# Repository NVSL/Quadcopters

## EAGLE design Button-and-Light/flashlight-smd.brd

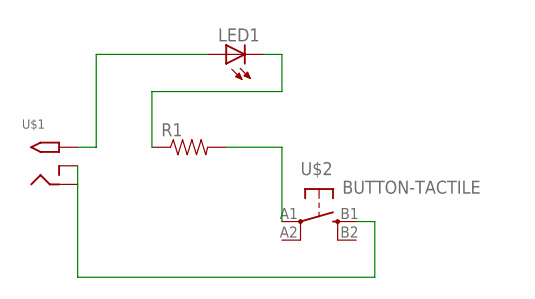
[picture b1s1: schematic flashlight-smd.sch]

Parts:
LED1: LED5MM
R1: RESISTORAXIAL-0.3; AXIAL-0.3
U$1: 2.1MMJACKTHM; PJ-102A
U$2: BUTTON-TACTILE; TACTILE_SWITCH_TALL

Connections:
unnamed: R1.P$2 (2), U$2.A1
unnamed: LED1.K (C), R1.P$1 (1)
unnamed: LED1.A, U$1.TIP
unnamed: U$1.RING, U$1.RING_SW, U$2.B1 (S)

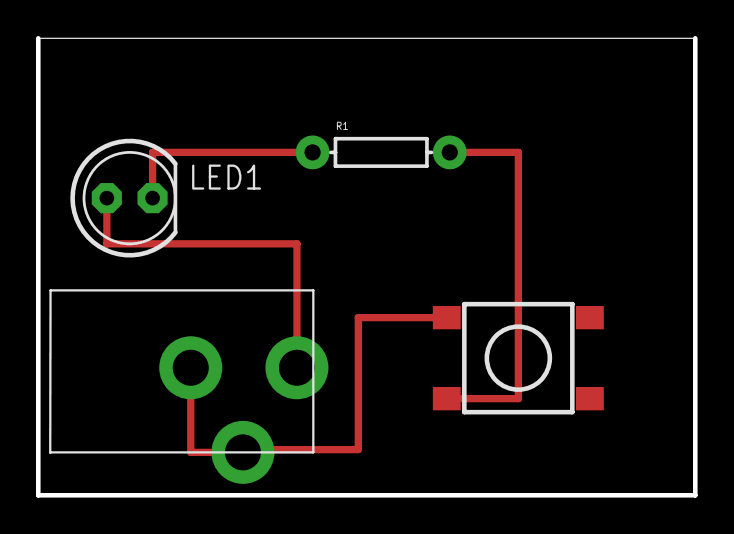
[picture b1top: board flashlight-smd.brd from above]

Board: 2 copper layers, 36.5 x 25.4 mm, 4 parts (0 on the bottom side), 4 nets.

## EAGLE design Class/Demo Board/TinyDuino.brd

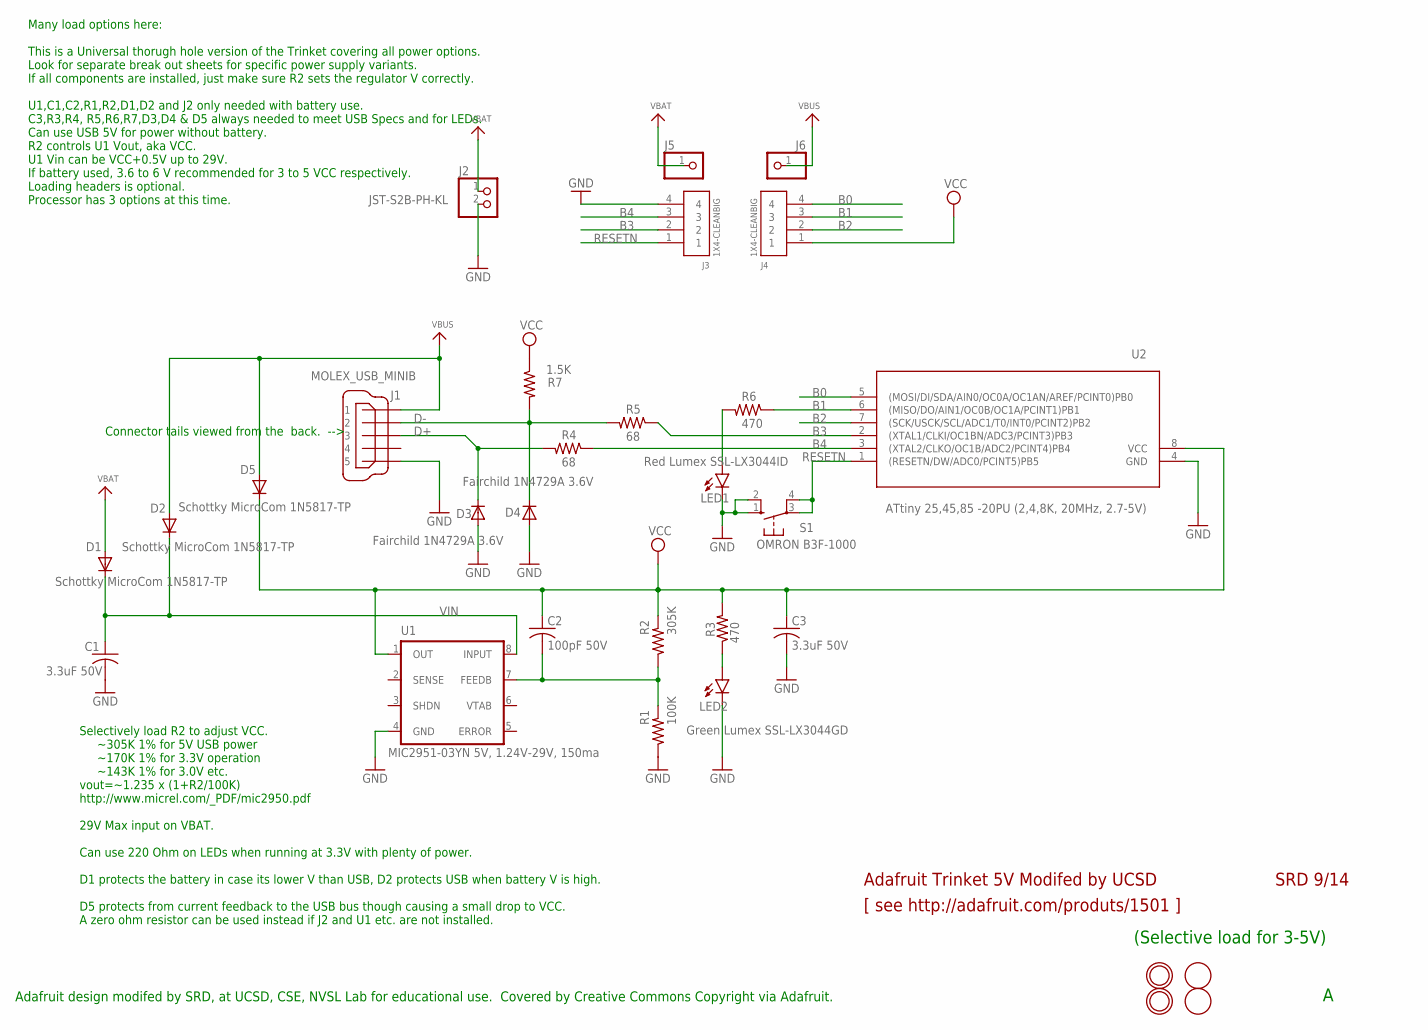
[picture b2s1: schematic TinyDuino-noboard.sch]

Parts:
C1, C3: 3.3uF 50V; C050-025X075; PARTNO FK20X7R1H335K
C2: 100pF 50V; C050-025X075; PARTNO FK28C0G1H101J
D1, D2, D5: Schottky MicroCom 1N5817-TP; DO41-7.6; PARTNO 1N5817-TP
D3, D4: Fairchild 1N4729A 3.6V; DO41-7.6; PARTNO 1N4729A
J1: MOLEX_USB_MINIB; 32005-601-ROUND; PARTNO 0548190519
J2: JST-S2B-PH-KL; JST_S2B_PH_KL; PARTNO JST_S2B_PH_KL
J3, J4: 1X4-CLEANBIG; 1X04-CLEANBIG
J5, J6: PINHD-1X1CB; 1X01-CLEANBIG
LED1: Red Lumex SSL-LX3044ID; LED3MM; PARTNO SSL-LX3044ID
LED2: Green Lumex SSL-LX3044GD; LED3MM; PARTNO SSL-LX3044GD
R1: 100K; 0204/7; PARTNO MFR-25FBF52-100K
R2: 305K; 0204/7; PARTNO MFR-25FBF52-301K
R3, R6: 470; 0204/7; PARTNO CFR-12JB-52-470R
R4, R5: 68; 0204/7; PARTNO CFR-12JB-52-68R
R7: 1.5K; 0204/7; PARTNO CFR-12JB-52-1K5
S1: OMRON B3F-1000; B3F-10XX; PARTNO B3F-1000
U1: MIC2951-03YN 5V, 1.24V-29V, 150ma; DIL08; PARTNO MIC2951-03YN
U2: ATtiny 25,45,85 -20PU (2,4,8K, 20MHz, 2.7-5V); DIL08; PARTNO ATTINY85-20PU-ND
Z1, Z2: MOUNTINGHOLE2.0; MOUNTINGHOLE_2.0_PLATED
Z3, Z4: FIDUCIAL; FIDUCIAL_1MM

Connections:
B0: J4.4, U2.5 ((MOSI/DI/SDA/AIN0/OC0A/OC1AN/AREF/PCINT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)
B1: J4.3, R6.1, U2.6 ((MISO/DO/AIN1/OC0B/OC1A/PCINT1)PB1)
B2: J4.2, U2.7 ((SCK/USCK/SCL/ADC1/T0/INT0/PCINT2)PB2)
B3: J3.2, R5.1, U2.2 ((XTAL1/CLKI/OC1BN/ADC3/PCINT3)PB3)
B4: J3.3, R4.1, U2.3 ((XTAL2/CLKO/OC1B/ADC2/PCINT4)PB4)
D+: D3.C, J1.3, R4.2
D-: D4.C, J1.2, R5.2, R7.2
GND: C1.2, C3.2, D3.A, D4.A, J1.5, J2.2, J3.4, LED1.K (C), LED2.K (C), R1.1, S1.1 (S), S1.2 (S1), U1.4 (GND), U2.4 (GND)
unnamed: LED1.A, R6.2
unnamed: LED2.A, R3.1
unnamed: C2.2, R1.2, R2.1, U1.7 (FEEDB)
RESETN: J3.1, S1.3, S1.4 (P1), U2.1 ((RESETN/DW/ADC0/PCINT5)PB5)
VBAT: D1.A, J2.1, J5.1
VBUS: D2.A, D5.A, J1.1, J6.1
VCC: C2.1, C3.1, D5.C, J4.1, R2.2, R3.2, R7.1, U1.1 (OUT), U2.8 (VCC)
VIN: C1.1, D1.C, D2.C, U1.8 (INPUT)

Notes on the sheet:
Adafruit Trinket 5V Modifed by UCSD
[ see http://adafruit.com/produts/1501 ]
SRD 9/14
Adafruit design modifed by SRD, at UCSD, CSE, NVSL Lab for educational use. Covered by Creative Commons Copyright via Adafruit.
(Selective load for 3-5V)
Selectively load R2 to adjust VCC. ~305K 1% for 5V USB power ~170K 1% for 3.3V operation ~143K 1% for 3.0V etc. vout=~1.235 x (1+R2/100K) http://www.micrel.com/_PDF/mic2950.pdf 29V Max input on VBAT. Can use 220 Ohm on LEDs when running at 3.3V with plenty of power. D1 protects the battery in case 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
Connector tails viewed from the back. -->
Many load options here: This is a Universal thorugh hole version of the Trinket covering all power options. Look for separate break out sheets for specific power supply variants. If all components are installed, just make sure R2 sets the regulator V correctly. U1,C1,C2,R1,R2,D1,D2 and J2 only need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

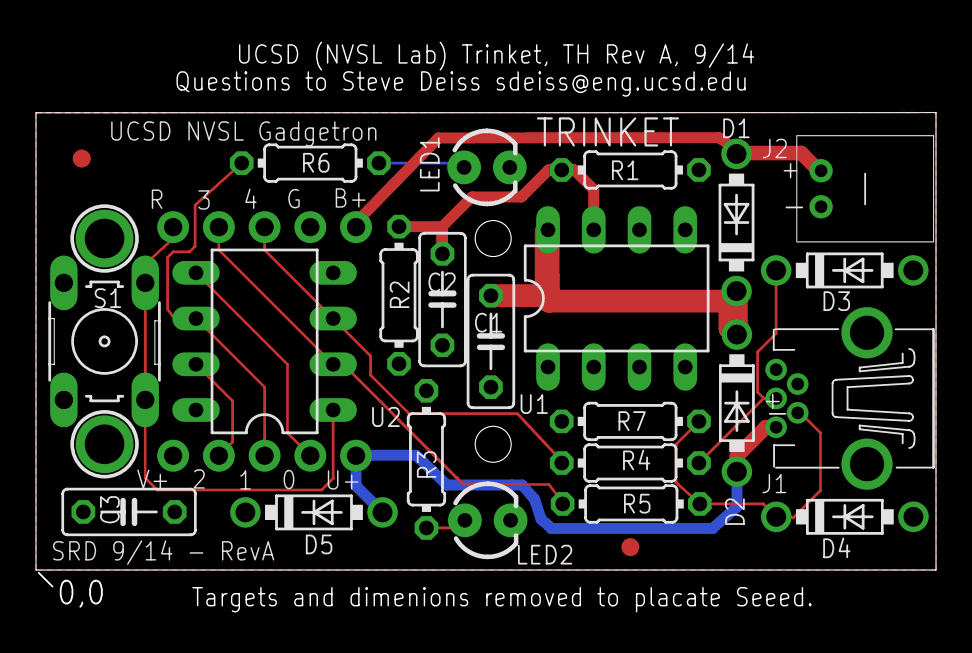
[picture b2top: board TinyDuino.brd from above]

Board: 2 copper layers, 50.0 x 26.3 mm, 30 parts (0 on the bottom side), 16 nets.

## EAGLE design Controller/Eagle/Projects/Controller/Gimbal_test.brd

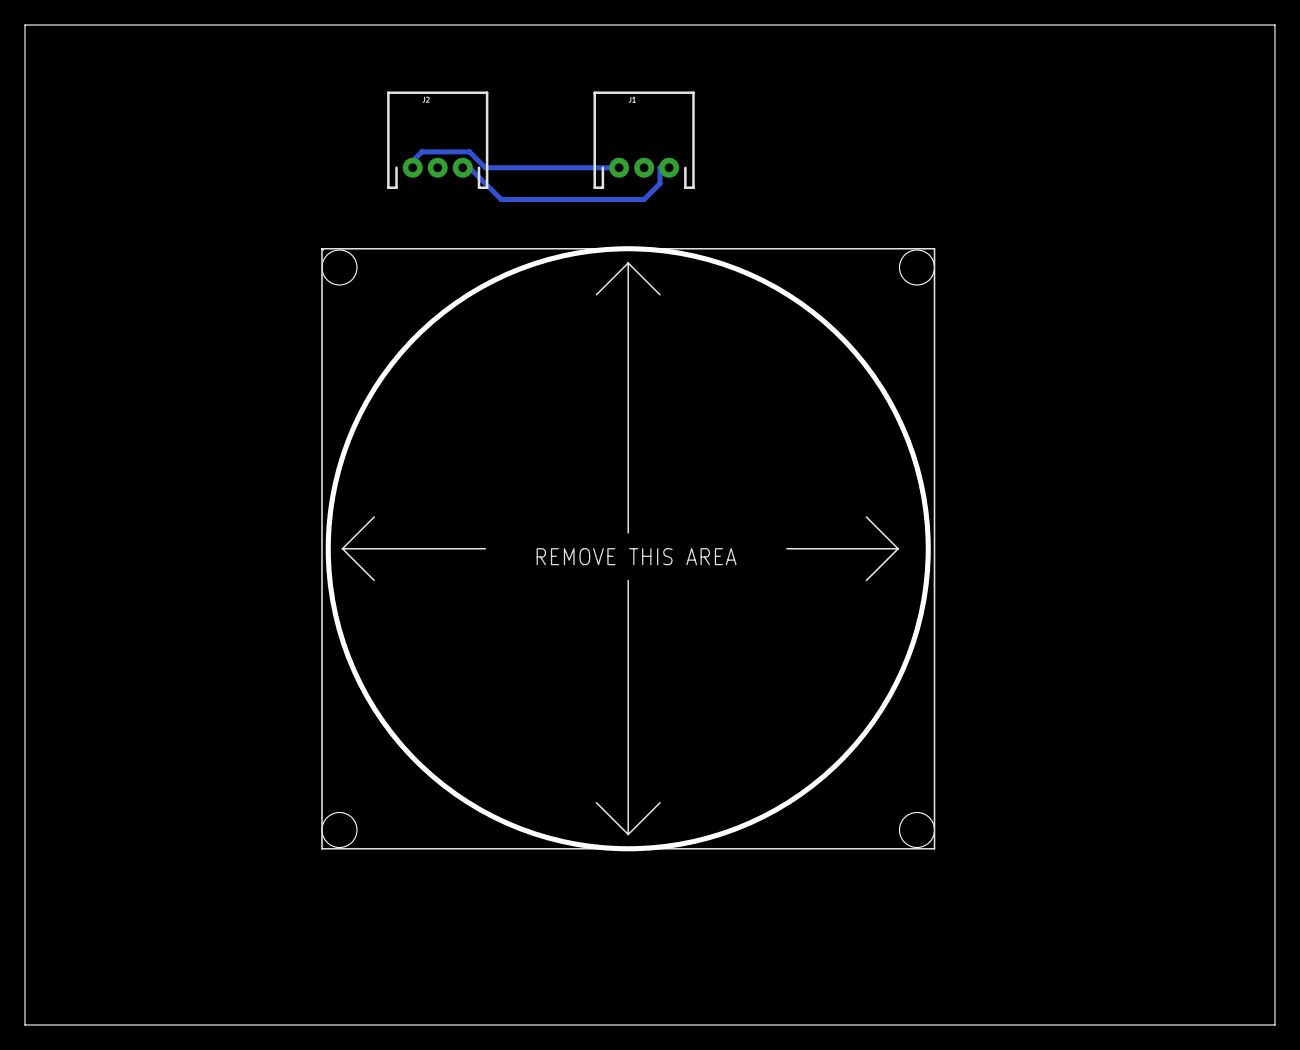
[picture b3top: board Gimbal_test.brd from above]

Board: 2 copper layers, 100.0 x 80.0 mm, 3 parts (0 on the bottom side), 2 nets.

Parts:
J1, J2: GIMBAL_3PIN; JST-3-PTH
U$1: GIMBAL_MOUNT; GIMBAL_FOOTPRINT

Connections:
GND: J1.3, J2.3
VDD: J1.1, J2.1

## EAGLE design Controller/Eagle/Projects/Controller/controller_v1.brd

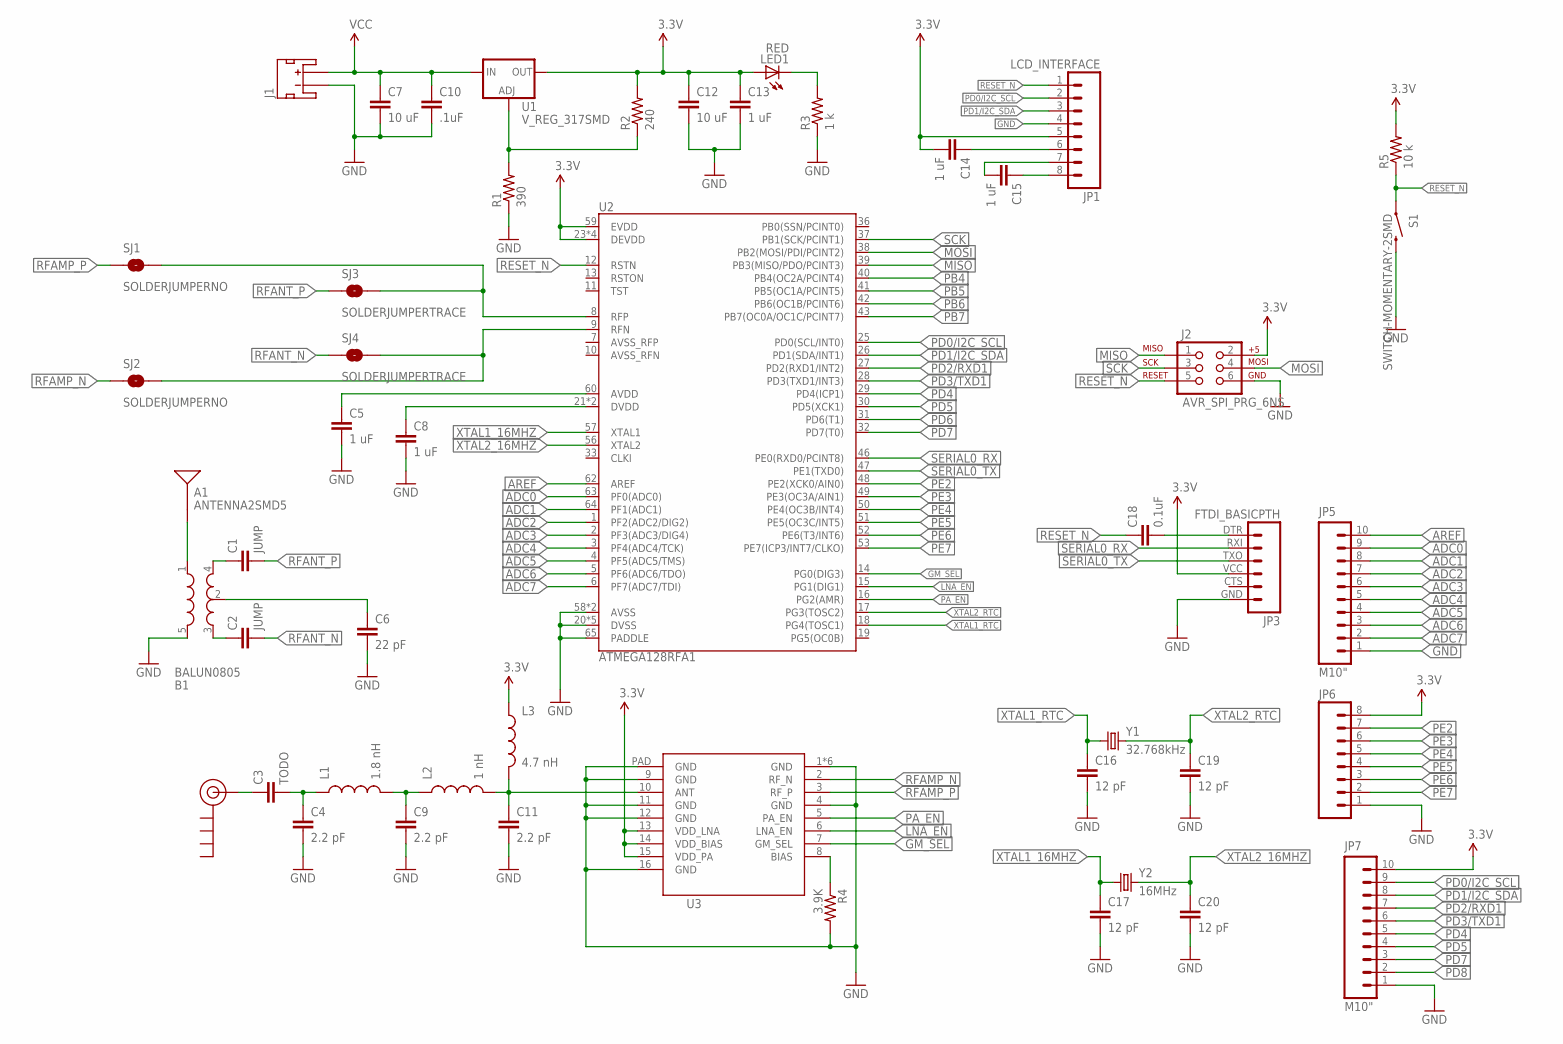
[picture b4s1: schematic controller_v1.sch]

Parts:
A1: ANTENNA2SMD5; ANTENNA-CHIP5
B1: BALUN0805; BALUN
C1, C2: JUMP; 0805
C3: TODO; 0805
C4, C9, C11: 2.2 pF; 0805
C5, C8, C13, C14, C15: 1 uF; 0805
C6: 22 pF; 0805
C7, C12: 10 uF; 0805
C10: .1uF; 0805
C16, C17, C19, C20: 12 pF; 0805
C18: 0.1uF; 0805
J1: BATT; JST-2-SMD
J2: AVR_SPI_PRG_6NS; 2X3-NS
J$1: SMA_EDGE; SMA-EDGE
JP1: LCD_INTERFACE; 1X08
JP3: FTDI_BASICPTH; FTDI_BASIC
JP5, JP7: M10"; 1X10
JP6: M081X08; 1X08
L1: 1.8 nH; 0805
L2: 1 nH; 0805
L3: 4.7 nH; 0805
LED1: RED; LED-0603
R1: 390; 0805
R2: 240; 0805
R3: 1 k; 0805
R4: 3.9K; 0805
R5: 10 k; 0805
S1: SWITCH-MOMENTARY-2SMD; TACTILE_SWITCH_SMD
SJ1, SJ2: SOLDERJUMPERNO; SJ_2S-NO
SJ3, SJ4: SOLDERJUMPERTRACE; SJ_2S-TRACE
U1: V_REG_317SMD; SOT223
U2: ATMEGA128RFA1; QFN-64
U3: RF_AMPLIFIER; QFN65P400X400X100-17N
Y1: 32.768kHz; CRYSTAL-32KHZ-SMD
Y2: 16MHz; CRYSTAL-SMD-5X3

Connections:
3.3V: C12.1, C13.1, C14.2, J2.2, JP1.5, JP3.VCC (4), JP6.8, JP7.10, L3.1, LED1.A, R2.2, R5.2, U1.2 (OUT), U2.23 (DEVDD), U2.34 (DEVDD), U2.44 (DEVDD), U2.54 (DEVDD), U2.59 (EVDD), U3.13 (VDD_LNA), U3.14 (VDD_BIAS), U3.15 (VDD_PA)
ADC0: JP5.9, U2.63 (PF0(ADC0))
ADC1: JP5.8, U2.64 (PF1(ADC1))
ADC2: JP5.7, U2.1 (PF2(ADC2/DIG2))
ADC3: JP5.6, U2.2 (PF3(ADC3/DIG4))
ADC4: JP5.5, U2.3 (PF4(ADC4/TCK))
ADC5: JP5.4, U2.4 (PF5(ADC5/TMS))
ADC6: JP5.3, U2.5 (PF6(ADC6/TDO))
ADC7: JP5.2, U2.6 (PF7(ADC7/TDI))
AREF: JP5.10, U2.62 (AREF)
GM_SEL: U2.14 (PG0(DIG3)), U3.7 (GM_SEL)
GND: B1.5 (GND), C4.2, C5.2, C6.2, C7.2, C8.2, C9.2, C10.2, C11.2, C12.2, C13.2, C16.2, C17.2, C19.2, C20.2, J1.1 (-), J2.6, JP1.4, JP3.GND (6), JP5.1, JP6.1, JP7.1, R1.1, R3.1, R4.2, S1.3 (2), U2.20 (DVSS), U2.24 (DVSS), U2.35 (DVSS), U2.45 (DVSS), U2.55 (DVSS), U2.58 (AVSS), U2.61 (AVSS), U2.65 (PADDLE), U3.1 (GND), U3.4 (GND), U3.9 (GND), U3.11 (GND), U3.12 (GND), U3.16 (GND), U3.P$1 (GND), U3.P$2 (GND), U3.P$3 (GND), U3.P$4 (GND), U3.P$5 (GND), U3.PAD (GND)
LNA_EN: U2.15 (PG1(DIG1)), U3.6 (LNA_EN)
MISO: J2.1, U2.39 (PB3(MISO/PDO/PCINT3))
MOSI: J2.4, U2.38 (PB2(MOSI/PDI/PCINT2))
unnamed: C9.1, L1.2, L2.1
unnamed: C18.2, JP3.DTR (1)
unnamed: C11.1, L2.2, L3.2, U3.10 (ANT)
unnamed: C3.2, C4.1, L1.1
unnamed: SJ1.2, SJ3.2, U2.8 (RFP)
unnamed: SJ2.2, SJ4.2, U2.9 (RFN)
unnamed: R4.1, U3.8 (BIAS)
unnamed: C3.1, J$1.SIG (SIGNAL)
unnamed: B1.4 (OUT1), C1.1
unnamed: B1.3 (OUT2), C2.1
unnamed: B1.2 (GND), C6.1
unnamed: A1.FEED, B1.1 (IN)
unnamed: R1.2, R2.1, U1.1 (ADJ)
unnamed: LED1.C, R3.2
unnamed: C5.1, U2.60 (AVDD)
unnamed: C8.1, U2.21 (DVDD), U2.22 (DVDD)
unnamed: C14.1, JP1.6
unnamed: C15.2, JP1.7
unnamed: C15.1, JP1.8
PA_EN: U2.16 (PG2(AMR)), U3.5 (PA_EN)
PB4: U2.40 (PB4(OC2A/PCINT4))
PB5: U2.41 (PB5(OC1A/PCINT5))
PB6: U2.42 (PB6(OC1B/PCINT6))
PB7: U2.43 (PB7(OC0A/OC1C/PCINT7))
PD0/I2C_SCL: JP1.2, JP7.9, U2.25 (PD0(SCL/INT0))
PD1/I2C_SDA: JP1.3, JP7.8, U2.26 (PD1(SDA/INT1))
PD2/RXD1: JP7.7, U2.27 (PD2(RXD1/INT2))
PD3/TXD1: JP7.6, U2.28 (PD3(TXD1/INT3))
PD4: JP7.5, U2.29 (PD4(ICP1))
PD5: JP7.4, U2.30 (PD5(XCK1))
PD6: U2.31 (PD6(T1))
PD7: JP7.3, U2.32 (PD7(T0))
PD8: JP7.2
PE2: JP6.7, U2.48 (PE2(XCK0/AIN0))
PE3: JP6.6, U2.49 (PE3(OC3A/AIN1))
PE4: JP6.5, U2.50 (PE4(OC3B/INT4))
PE5: JP6.4, U2.51 (PE5(OC3C/INT5))
PE6: JP6.3, U2.52 (PE6(T3/INT6))
PE7: JP6.2, U2.53 (PE7(ICP3/INT7/CLKO))
RESET_N: C18.1, J2.5, JP1.1, R5.1, S1.1, U2.12 (RSTN)
RFAMP_N: SJ2.1, U3.2 (RF_N)
RFAMP_P: SJ1.1, U3.3 (RF_P)
RFANT_N: C2.2, SJ4.1
RFANT_P: C1.2, SJ3.1
SCK: J2.3, U2.37 (PB1(SCK/PCINT1))
SERIAL0_RX: JP3.RXI (2), U2.46 (PE0(RXD0/PCINT8))
SERIAL0_TX: JP3.TXO (3), U2.47 (PE1(TXD0))
VCC: C7.1, C10.1, J1.2 (+), U1.3 (IN)
XTAL1_16MHZ: C17.1, U2.57 (XTAL1), Y2.1
XTAL1_RTC: C16.1, U2.18 (PG4(TOSC1)), Y1.X1 (1)
XTAL2_16MHZ: C20.1, U2.56 (XTAL2), Y2.3 (2)
XTAL2_RTC: C19.1, U2.17 (PG3(TOSC2)), Y1.X2 (2)

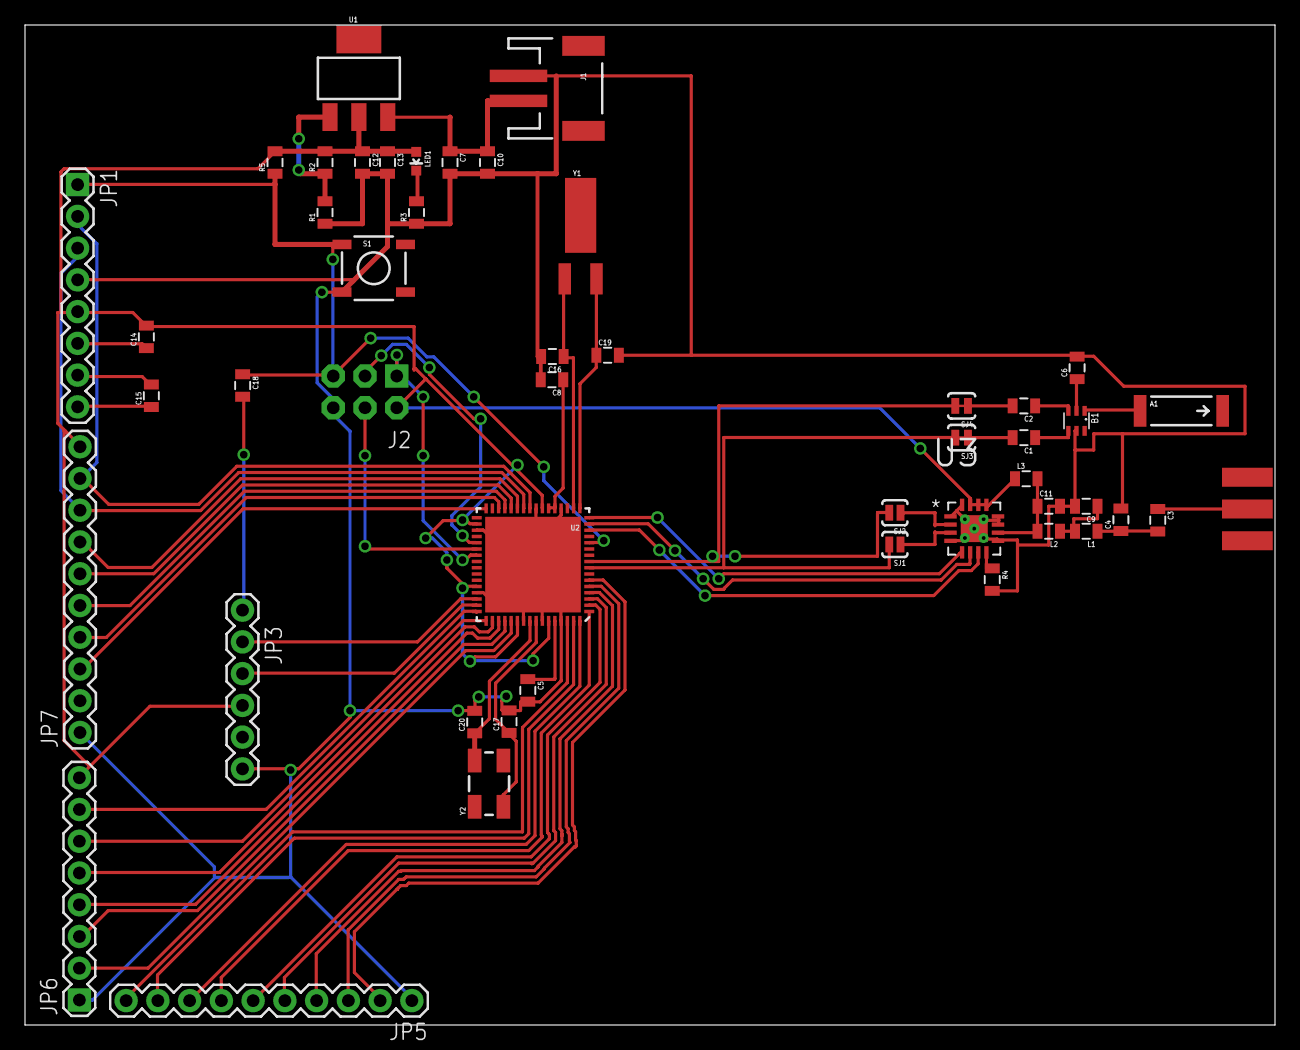
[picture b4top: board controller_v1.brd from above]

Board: 2 copper layers, 100.0 x 80.0 mm, 49 parts (0 on the bottom side), 61 nets.

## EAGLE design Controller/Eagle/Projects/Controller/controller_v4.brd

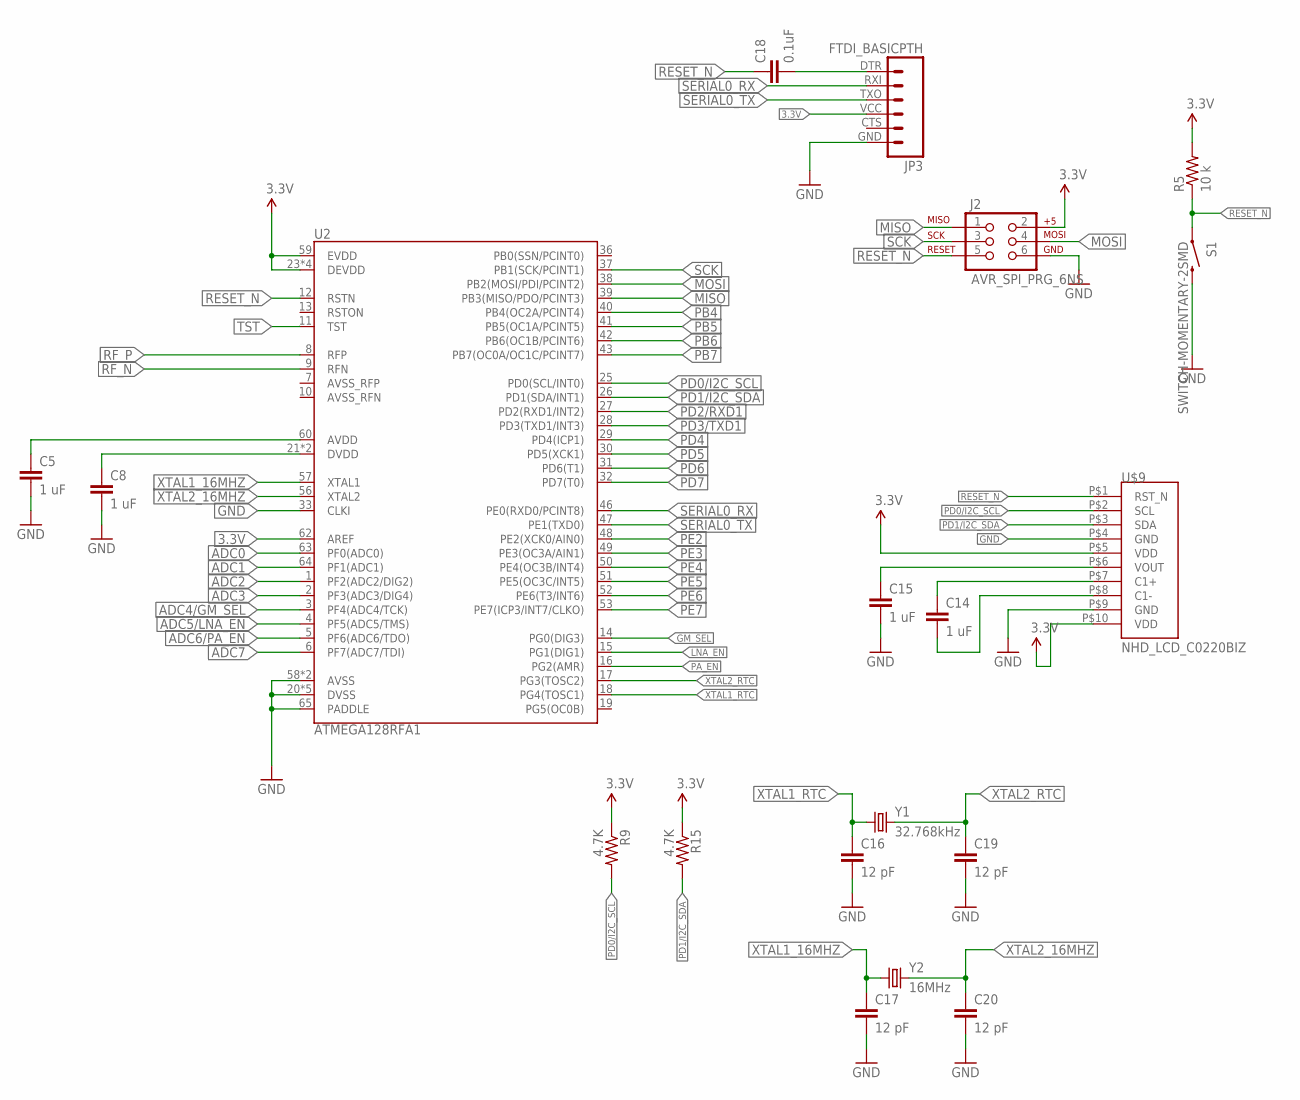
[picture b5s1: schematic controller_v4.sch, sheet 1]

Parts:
C5, C8, C14, C15: 1 uF; 0805
C16, C17, C19, C20: 12 pF; 0805
C18: 0.1uF; 0805
J2: AVR_SPI_PRG_6NS; 2X3-NS
JP3: FTDI_BASICPTH; FTDI_BASIC
R5: 10 k; 0805
R9, R15: 4.7K; 0805
S1: SWITCH-MOMENTARY-2SMD; TACTILE_SWITCH_SMD
U2: ATMEGA128RFA1; QFN-64
U$9: NHD_LCD_C0220BIZ; 1X08-2MMPTH-LCD
Y1: 32.768kHz; CRYSTAL-32KHZ-SMD
Y2: 16MHz; CRYSTAL-SMD-5X3

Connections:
3.3V: J2.2, JP3.VCC (4), R5.2, R9.1, R15.1, U2.23 (DEVDD), U2.34 (DEVDD), U2.44 (DEVDD), U2.54 (DEVDD), U2.59 (EVDD), U2.62 (AREF), U$9.P$5 (VDD), U$9.P$10 (VDD); also elsewhere on the board
ADC0: U2.63 (PF0(ADC0)); also elsewhere on the board
ADC1: U2.64 (PF1(ADC1)); also elsewhere on the board
ADC2: U2.1 (PF2(ADC2/DIG2)); also elsewhere on the board
ADC3: U2.2 (PF3(ADC3/DIG4)); also elsewhere on the board
ADC4/GM_SEL: U2.3 (PF4(ADC4/TCK)); also elsewhere on the board
ADC5/LNA_EN: U2.4 (PF5(ADC5/TMS)); also elsewhere on the board
ADC6/PA_EN: U2.5 (PF6(ADC6/TDO)); also elsewhere on the board
ADC7: U2.6 (PF7(ADC7/TDI))
GM_SEL: U2.14 (PG0(DIG3))
GND: C5.2, C8.2, C15.2, C16.2, C17.2, C19.2, C20.2, J2.6, JP3.GND (6), S1.3 (2), U2.20 (DVSS), U2.24 (DVSS), U2.33 (CLKI), U2.35 (DVSS), U2.45 (DVSS), U2.55 (DVSS), U2.58 (AVSS), U2.61 (AVSS), U2.65 (PADDLE), U$9.P$4 (GND), U$9.P$9 (GND); also elsewhere on the board
LNA_EN: U2.15 (PG1(DIG1))
MISO: J2.1, U2.39 (PB3(MISO/PDO/PCINT3))
MOSI: J2.4, U2.38 (PB2(MOSI/PDI/PCINT2))
unnamed: C18.2, JP3.DTR (1)
unnamed: C14.1, U$9.P$7 (C1+)
unnamed: C5.1, U2.60 (AVDD)
unnamed: C8.1, U2.21 (DVDD), U2.22 (DVDD)
unnamed: C14.2, U$9.P$8 (C1-)
PA_EN: U2.16 (PG2(AMR))
PB4: U2.40 (PB4(OC2A/PCINT4)); also elsewhere on the board
PB5: U2.41 (PB5(OC1A/PCINT5)); also elsewhere on the board
PB6: U2.42 (PB6(OC1B/PCINT6)); also elsewhere on the board
PB7: U2.43 (PB7(OC0A/OC1C/PCINT7)); also elsewhere on the board
PD0/I2C_SCL: R9.2, U2.25 (PD0(SCL/INT0)), U$9.P$2 (SCL)
PD1/I2C_SDA: R15.2, U2.26 (PD1(SDA/INT1)), U$9.P$3 (SDA)
PD2/RXD1: U2.27 (PD2(RXD1/INT2)); also elsewhere on the board
PD3/TXD1: U2.28 (PD3(TXD1/INT3)); also elsewhere on the board
PD4: U2.29 (PD4(ICP1))
PD5: U2.30 (PD5(XCK1))
PD6: U2.31 (PD6(T1))
PD7: U2.32 (PD7(T0))
PE2: U2.48 (PE2(XCK0/AIN0))
PE3: U2.49 (PE3(OC3A/AIN1))
PE4: U2.50 (PE4(OC3B/INT4))
PE5: U2.51 (PE5(OC3C/INT5))
PE6: U2.52 (PE6(T3/INT6)); also elsewhere on the board
PE7: U2.53 (PE7(ICP3/INT7/CLKO)); also elsewhere on the board
RESET_N: C18.1, J2.5, R5.1, S1.1, U2.12 (RSTN), U$9.P$1 (RST_N)
RF_N: U2.9 (RFN); also elsewhere on the board
RF_P: U2.8 (RFP); also elsewhere on the board
SCK: J2.3, U2.37 (PB1(SCK/PCINT1))
SERIAL0_RX: JP3.RXI (2), U2.46 (PE0(RXD0/PCINT8))
SERIAL0_TX: JP3.TXO (3), U2.47 (PE1(TXD0))
TST: U2.11 (TST)
VOUT: C15.1, U$9.P$6 (VOUT)
XTAL1_16MHZ: C17.1, U2.57 (XTAL1), Y2.1
XTAL1_RTC: C16.1, U2.18 (PG4(TOSC1)), Y1.X1 (1)
XTAL2_16MHZ: C20.1, U2.56 (XTAL2), Y2.3 (2)
XTAL2_RTC: C19.1, U2.17 (PG3(TOSC2)), Y1.X2 (2)

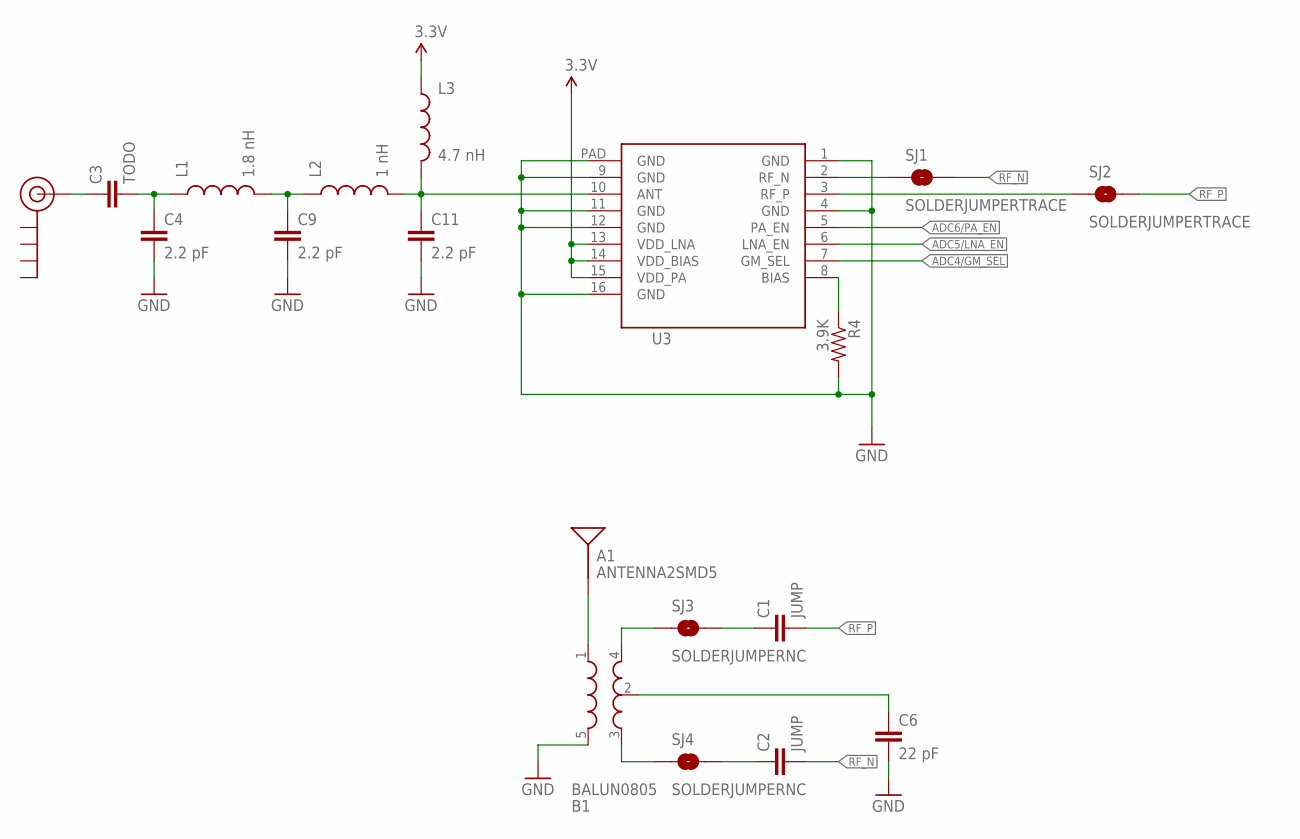
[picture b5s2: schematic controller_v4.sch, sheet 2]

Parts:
A1: ANTENNA2SMD5; ANTENNA-CHIP5
B1: BALUN0805; BALUN
C1, C2: JUMP; 0805
C3: TODO; 0805
C4, C9, C11: 2.2 pF; 0805
C6: 22 pF; 0805
J$1: SMA_EDGE; SMA-EDGE
L1: 1.8 nH; 0805
L2: 1 nH; 0805
L3: 4.7 nH; 0805
R4: 3.9K; 0805
SJ1, SJ2: SOLDERJUMPERTRACE; SJ_2S-TRACE
SJ3, SJ4: SOLDERJUMPERNC; SJ_2S
U3: RF_AMPLIFIER; QFN65P400X400X100-17N

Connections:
3.3V: L3.1, U3.13 (VDD_LNA), U3.14 (VDD_BIAS), U3.15 (VDD_PA); also elsewhere on the board
ADC4/GM_SEL: U3.7 (GM_SEL); also elsewhere on the board
ADC5/LNA_EN: U3.6 (LNA_EN); also elsewhere on the board
ADC6/PA_EN: U3.5 (PA_EN); also elsewhere on the board
GND: B1.5 (GND), C4.2, C6.2, C9.2, C11.2, R4.2, U3.1 (GND), U3.4 (GND), U3.9 (GND), U3.11 (GND), U3.12 (GND), U3.16 (GND), U3.PAD (GND); also elsewhere on the board
unnamed: C9.1, L1.2, L2.1
unnamed: C11.1, L2.2, L3.2, U3.10 (ANT)
unnamed: C3.2, C4.1, L1.1
unnamed: SJ1.1, U3.2 (RF_N)
unnamed: R4.1, U3.8 (BIAS)
unnamed: C3.1, J$1.SIG (SIGNAL)
unnamed: B1.4 (OUT1), SJ3.1
unnamed: B1.3 (OUT2), SJ4.1
unnamed: B1.2 (GND), C6.1
unnamed: A1.FEED, B1.1 (IN)
unnamed: C1.1, SJ3.2
unnamed: C2.1, SJ4.2
unnamed: SJ2.1, U3.3 (RF_P)
RF_N: C2.2, SJ1.2; also elsewhere on the board
RF_P: C1.2, SJ2.2; also elsewhere on the board

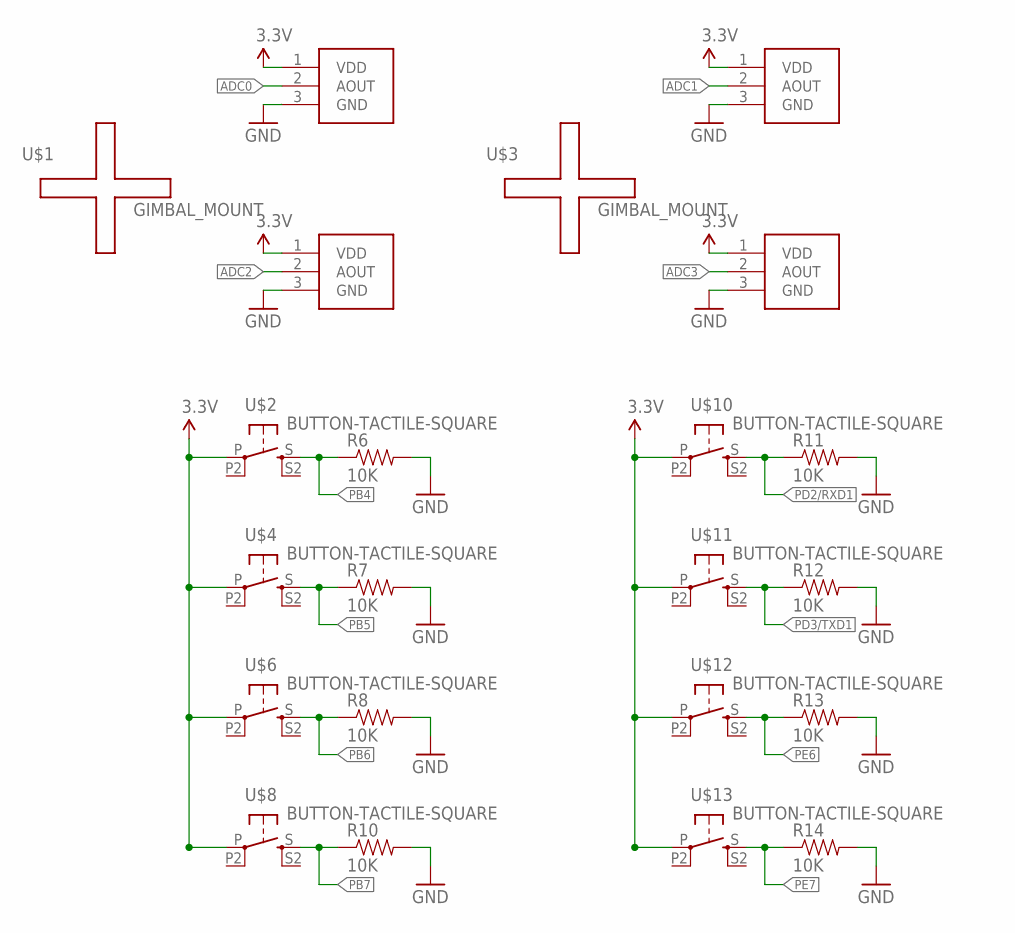
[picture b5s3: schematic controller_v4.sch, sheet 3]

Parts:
J3, J4, J5, J6: GIMBAL_3PIN; JST-3-PTH
R6, R7, R8, R10, R11, R12, R13, R14: 10K; 0805
U$1, U$3: GIMBAL_MOUNT; GIMBAL_FOOTPRINT
U$2, U$4, U$6, U$8, U$10, U$11, U$12, U$13: BUTTON-TACTILE-SQUARE; BUTTON-TACTILE-SQUARE-ADAFRUIT1010

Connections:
3.3V: J3.1 (VDD), J4.1 (VDD), J5.1 (VDD), J6.1 (VDD), U$2.P, U$4.P, U$6.P, U$8.P, U$10.P, U$11.P, U$12.P, U$13.P; also elsewhere on the board
ADC0: J6.2 (AOUT); also elsewhere on the board
ADC1: J3.2 (AOUT); also elsewhere on the board
ADC2: J5.2 (AOUT); also elsewhere on the board
ADC3: J4.2 (AOUT); also elsewhere on the board
GND: J3.3 (GND), J4.3 (GND), J5.3 (GND), J6.3 (GND), R6.2, R7.2, R8.2, R10.2, R11.2, R12.2, R13.2, R14.2; also elsewhere on the board
PB4: R6.1, U$2.S; also elsewhere on the board
PB5: R7.1, U$4.S; also elsewhere on the board
PB6: R8.1, U$6.S; also elsewhere on the board
PB7: R10.1, U$8.S; also elsewhere on the board
PD2/RXD1: R11.1, U$10.S; also elsewhere on the board
PD3/TXD1: R12.1, U$11.S; also elsewhere on the board
PE6: R13.1, U$12.S; also elsewhere on the board
PE7: R14.1, U$13.S; also elsewhere on the board

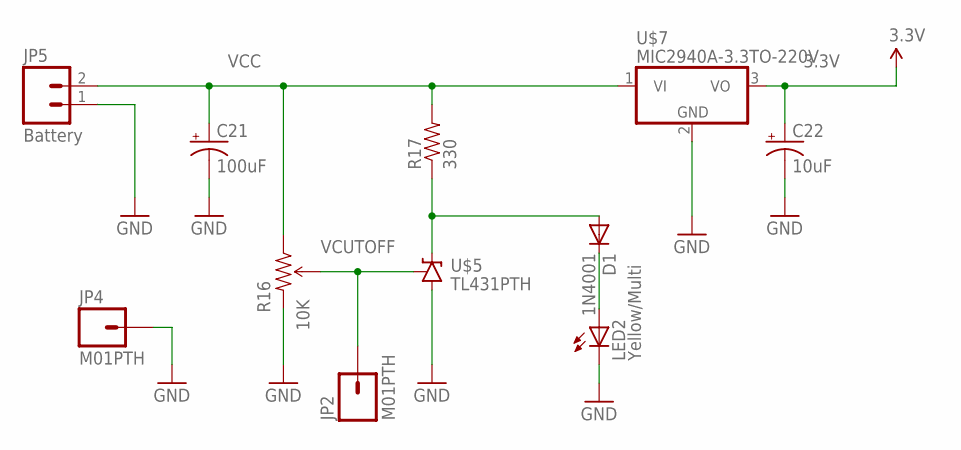
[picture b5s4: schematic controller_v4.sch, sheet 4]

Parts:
C21: 100uF; E3,5-8
C22: 10uF; E2,5-5
D1: 1N4001; DO41-10
JP2, JP4: M01PTH; 1X01
JP5: Battery; 1X02
LED2: Yellow/Multi; LED5MM
R16: 10K; 3386U
R17: 330; AXIAL-0.3
U$5: TL431PTH; TO-92
U$7: MIC2940A-3.3TO-220V; TO-220V

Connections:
3.3V: C22.+, U$7.3 (VO); also elsewhere on the board
GND: C21.-, C22.-, JP4.1, JP5.1, LED2.K (C), R16.3 (CW), U$5.2 (A), U$7.2 (GND); also elsewhere on the board
unnamed: D1.A, R17.P$1 (1), U$5.3 (C)
unnamed: D1.C, LED2.A
VCC: C21.+, JP5.2, R16.1 (CCW), R17.P$2 (2), U$7.1 (VI)
VCUTOFF: JP2.1, R16.2 (WIPER), U$5.1 (R)

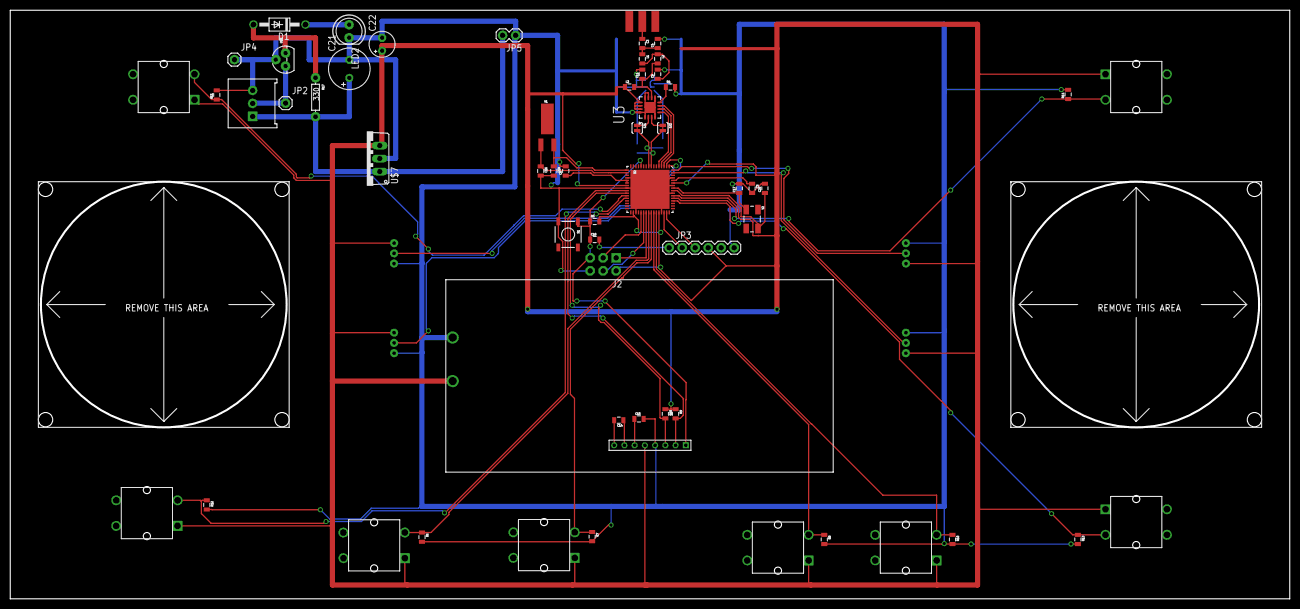
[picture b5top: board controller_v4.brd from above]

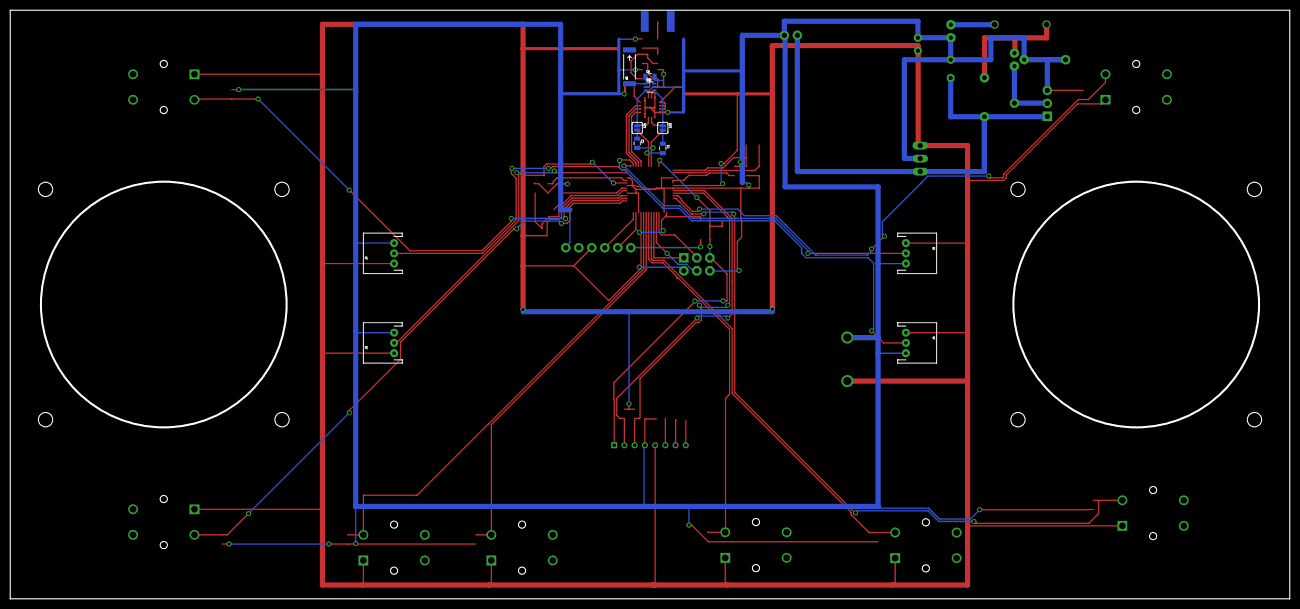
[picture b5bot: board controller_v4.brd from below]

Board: 2 copper layers, 250.0 x 115.0 mm, 71 parts (11 on the bottom side), 54 nets.

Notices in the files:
parts and their libraries:
microbuilder: This work is placed in the public domain, and may be freely used for commercial and non-commercial work with the following conditions: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
SparkFun-LED: Licensing: Creative Commons ShareAlike 4.0 International - https://creativecommons.org/licenses/by-sa/4.0
